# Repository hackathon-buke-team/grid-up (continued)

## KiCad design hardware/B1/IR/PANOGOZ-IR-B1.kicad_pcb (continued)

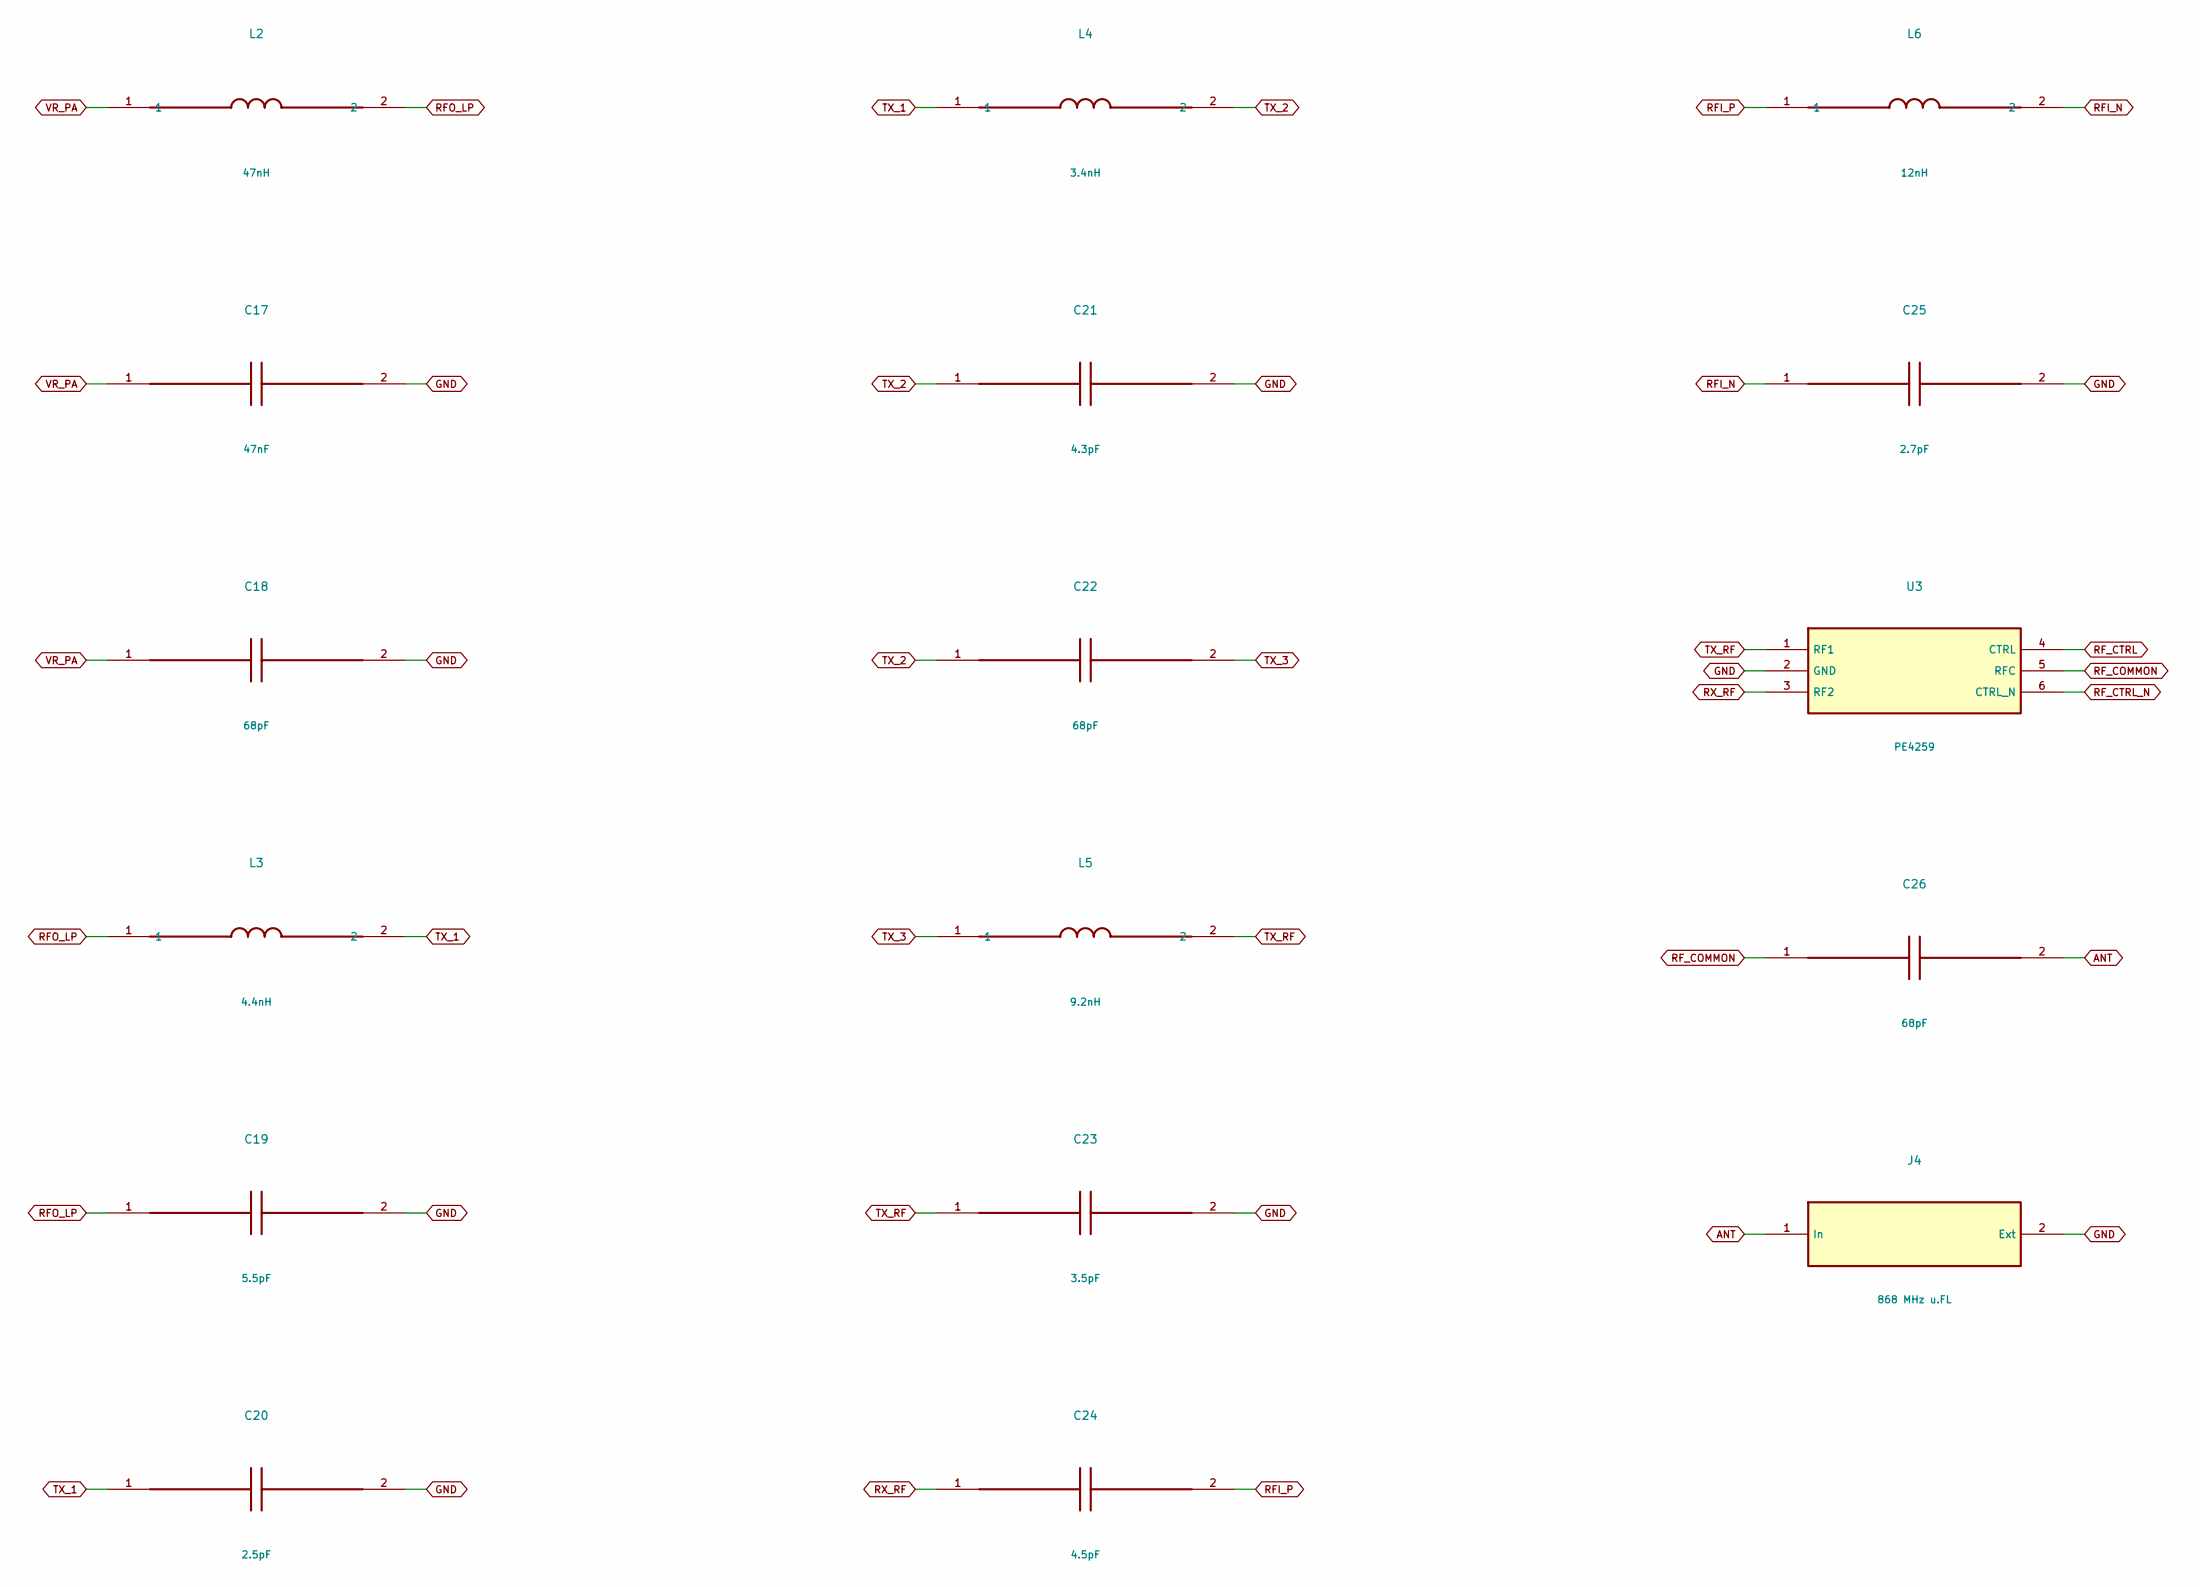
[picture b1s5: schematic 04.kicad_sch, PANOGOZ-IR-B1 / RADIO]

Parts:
C17: 47nF; C_0402_1005Metric; MPN X7R 16V 47nF
C18, C22, C26: 68pF; C_0402_1005Metric; MPN X7R 16V 68pF
C19: 5.5pF; C_0402_1005Metric; MPN X7R 16V 5.5pF
C20: 2.5pF; C_0402_1005Metric; MPN X7R 16V 2.5pF
C21: 4.3pF; C_0402_1005Metric; MPN X7R 16V 4.3pF
C23: 3.5pF; C_0402_1005Metric; MPN X7R 16V 3.5pF
C24: 4.5pF; C_0402_1005Metric; MPN X7R 16V 4.5pF
C25: 2.7pF; C_0402_1005Metric; MPN X7R 16V 2.7pF
J4: 868 MHz u.FL; U.FL_Hirose_U.FL-R-SMT-1_Vertical; MPN 868 MHz u.FL
L2: 47nH; L_0402_1005Metric; MPN 47nH
L3: 4.4nH; L_0402_1005Metric; MPN 4.4nH
L4: 3.4nH; L_0402_1005Metric; MPN 3.4nH
L5: 9.2nH; L_0402_1005Metric; MPN 9.2nH
L6: 12nH; L_0402_1005Metric; MPN 12nH
U3: PE4259; SOT-363_SC-70-6; MPN PE4259

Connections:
ANT: C26.2, J4.1 (In)
GND: C17.2, C18.2, C19.2, C20.2, C21.2, C23.2, C25.2, J4.2 (Ext), U3.2 (GND); also elsewhere on the board
RFI_N: C25.1, L6.2; also elsewhere on the board
RFI_P: C24.2, L6.1; also elsewhere on the board
RFO_LP: C19.1, L2.2, L3.1; also elsewhere on the board
RF_COMMON: C26.1, U3.5 (RFC)
RF_CTRL: U3.4 (CTRL); also elsewhere on the board
RF_CTRL_N: U3.6 (CTRL_N); also elsewhere on the board
RX_RF: C24.1, U3.3 (RF2)
TX_1: C20.1, L3.2, L4.1
TX_2: C21.1, C22.1, L4.2
TX_3: C22.2, L5.1
TX_RF: C23.1, L5.2, U3.1 (RF1)
VR_PA: C17.1, C18.1, L2.1; also elsewhere on the board

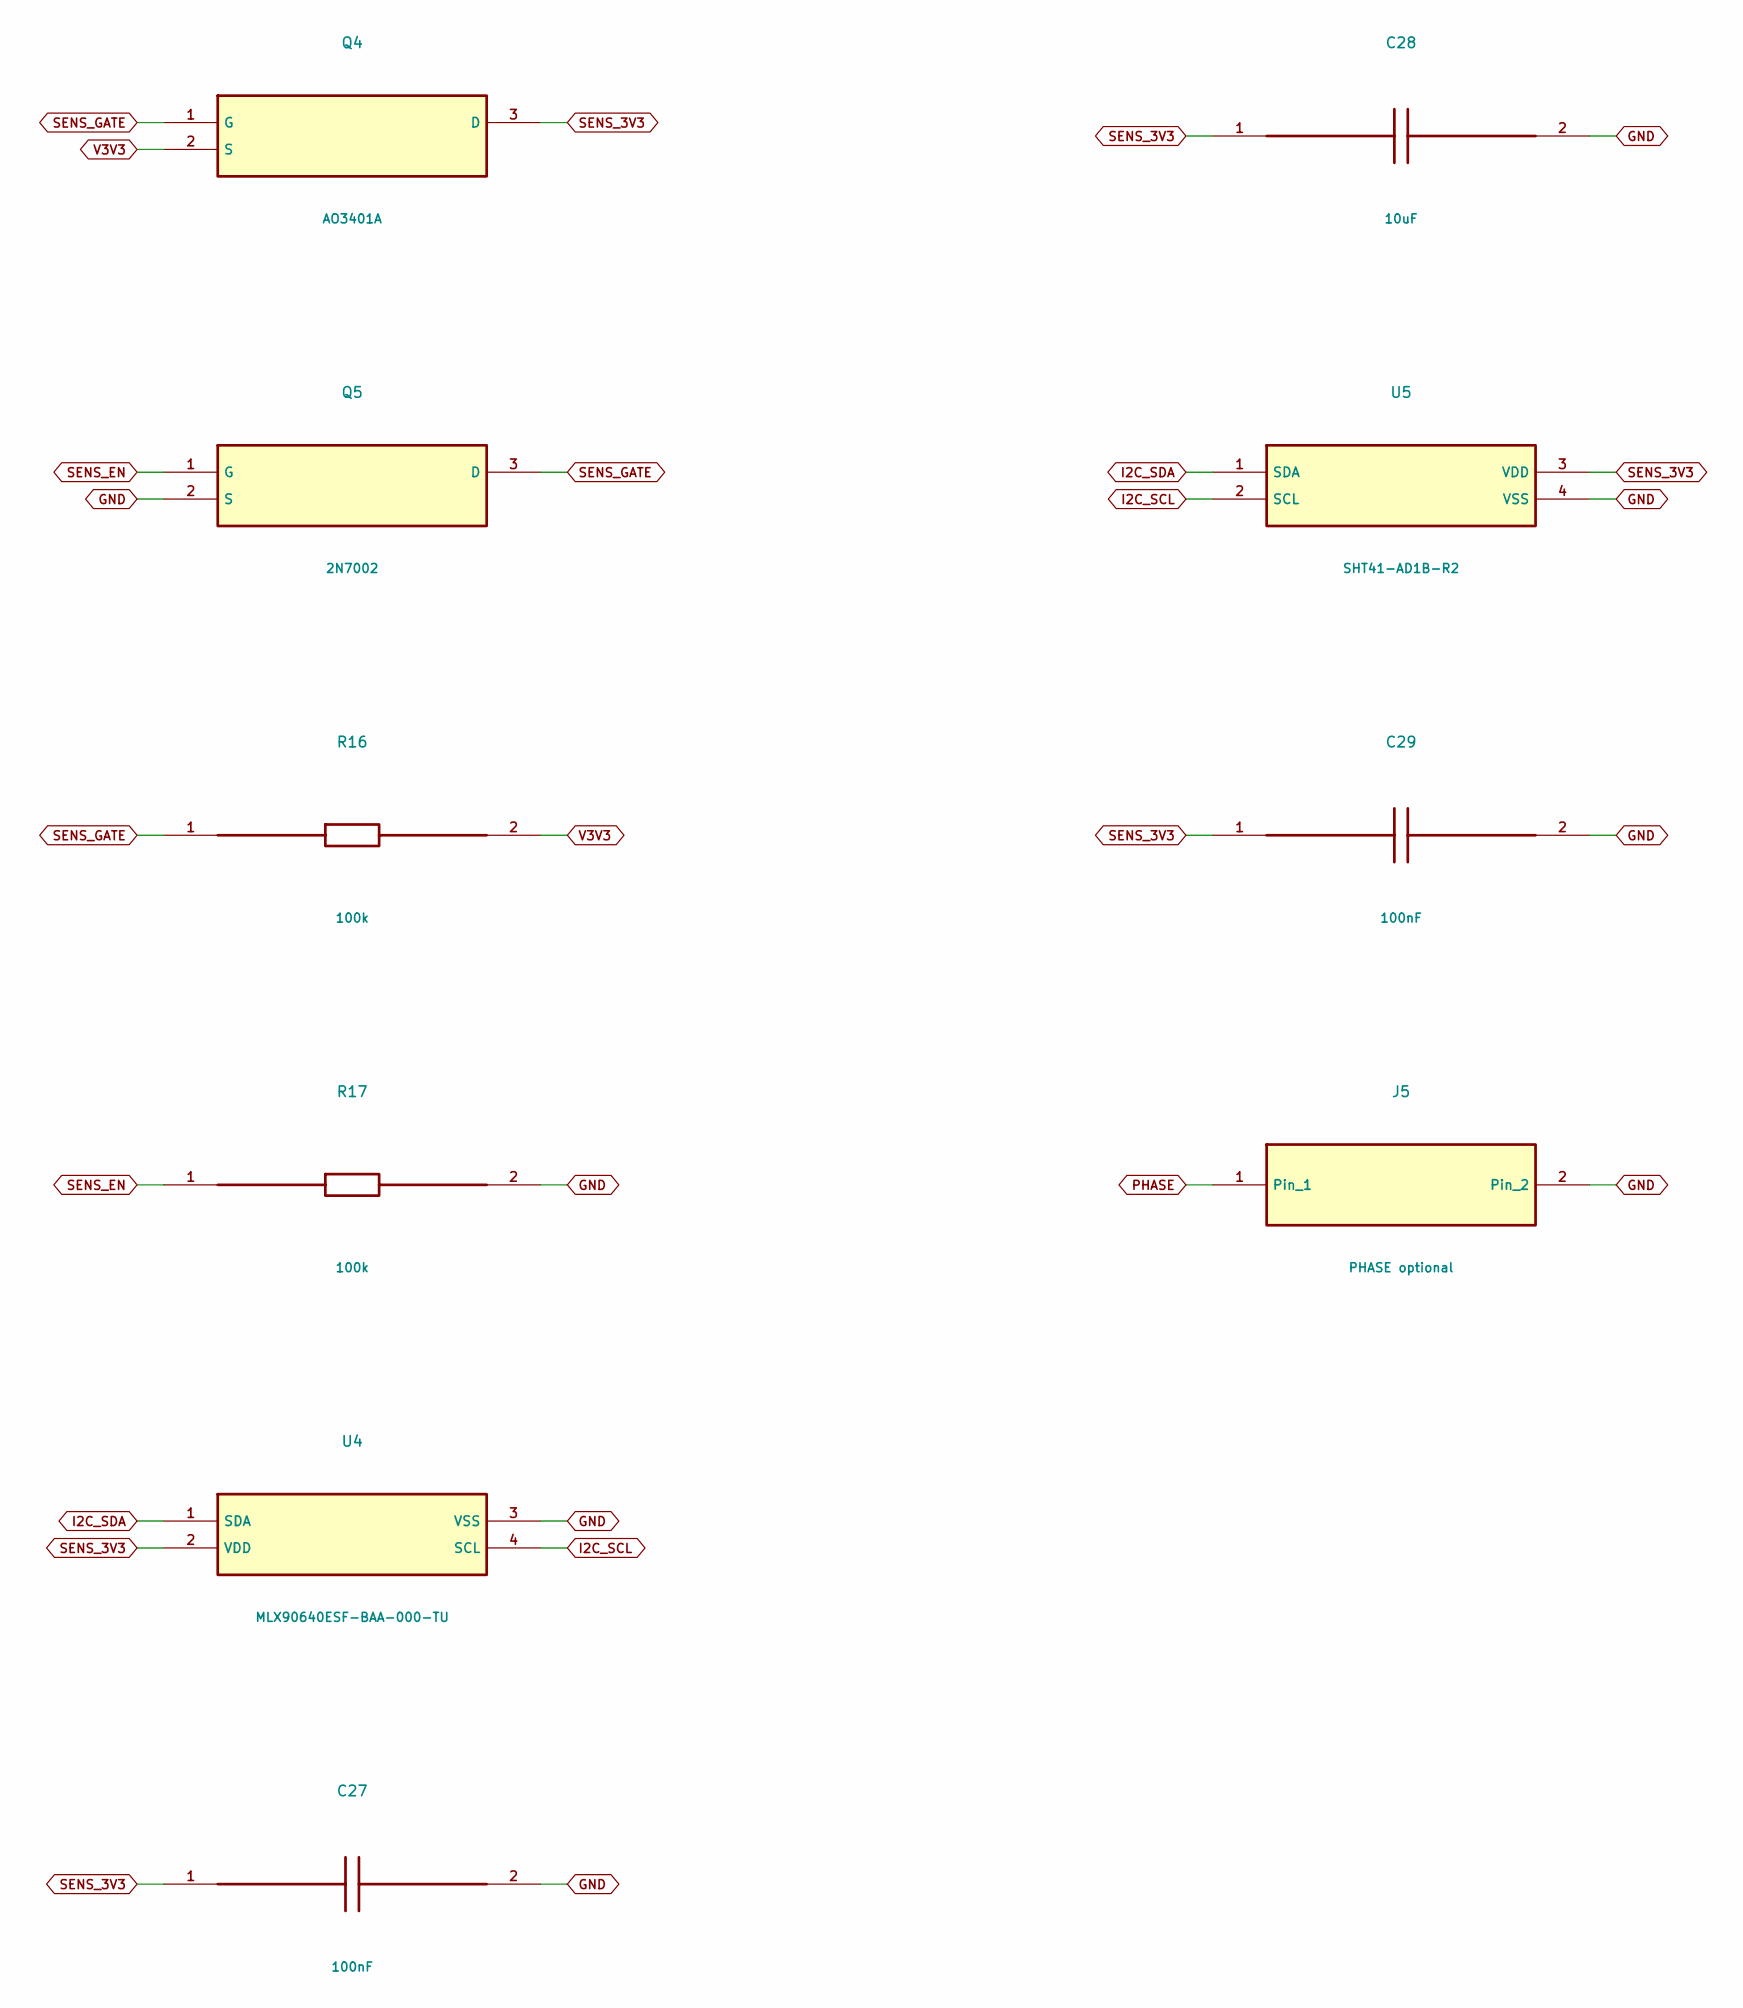
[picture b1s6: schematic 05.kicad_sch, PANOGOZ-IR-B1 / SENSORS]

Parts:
C27, C29: 100nF; C_0402_1005Metric; MPN X7R 16V 100nF
C28: 10uF; C_0805_2012Metric; MPN X7R 16V 10uF
J5: PHASE optional; JST_SH_SM02B-SRSS-TB_1x02-1MP_P1.00mm_Horizontal; MPN PHASE optional
Q4: AO3401A; SOT-23; MPN AO3401A
Q5: 2N7002; SOT-23; MPN 2N7002
R16, R17: 100k; R_0402_1005Metric; MPN 1% thick film 100k
U4: MLX90640ESF-BAA-000-TU; TO-39-4_Window; MPN MLX90640ESF-BAA-000-TU
U5: SHT41-AD1B-R2; Sensirion_DFN-4_1.5x1.5mm_P0.8mm_SHT4x_NoCentralPad; MPN SHT41-AD1B-R2

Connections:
GND: C27.2, C28.2, C29.2, J5.2, Q5.2 (S), R17.2, U4.3 (VSS), U5.4 (VSS); also elsewhere on the board
I2C_SCL: U4.4 (SCL), U5.2 (SCL); also elsewhere on the board
I2C_SDA: U4.1 (SDA), U5.1 (SDA); also elsewhere on the board
PHASE: J5.1; also elsewhere on the board
SENS_3V3: C27.1, C28.1, C29.1, Q4.3 (D), U4.2 (VDD), U5.3 (VDD); also elsewhere on the board
SENS_EN: Q5.1 (G), R17.1; also elsewhere on the board
SENS_GATE: Q4.1 (G), Q5.3 (D), R16.1
V3V3: Q4.2 (S), R16.2; also elsewhere on the board

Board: 4 copper layers, 70 parts (1 on the bottom side), 47 nets, no tracks yet.

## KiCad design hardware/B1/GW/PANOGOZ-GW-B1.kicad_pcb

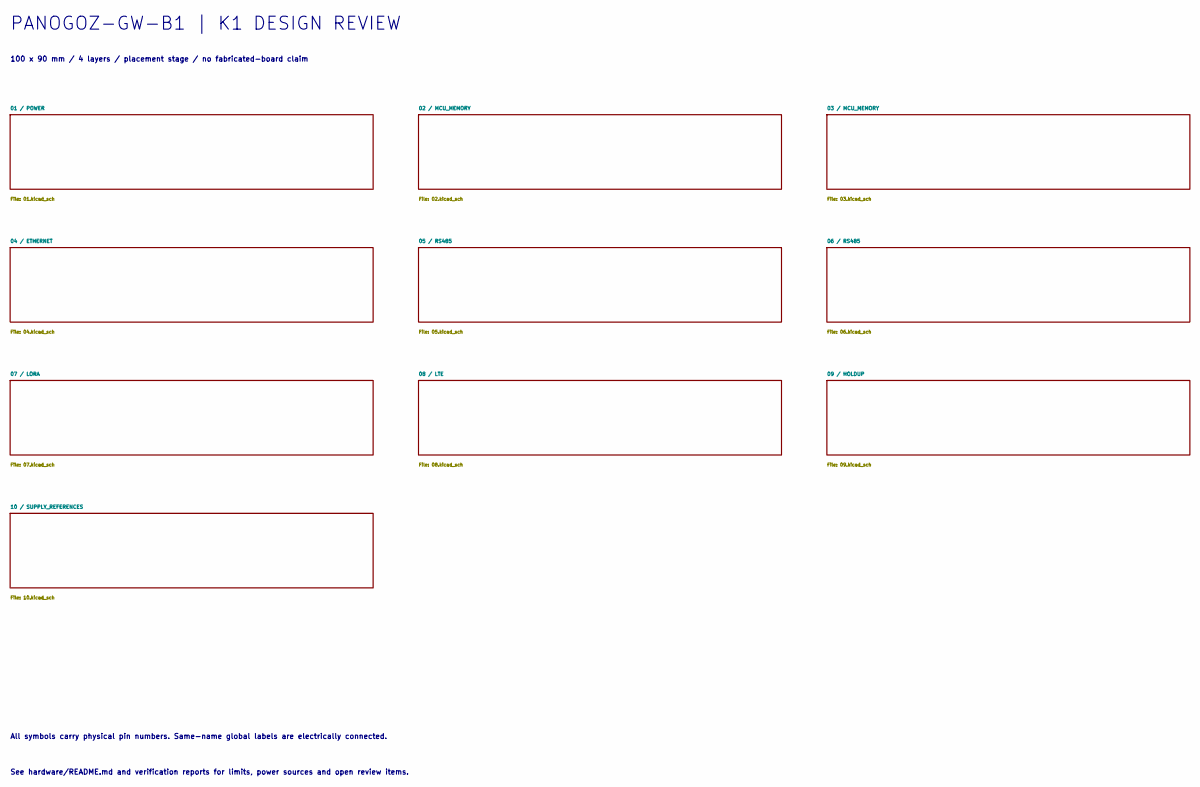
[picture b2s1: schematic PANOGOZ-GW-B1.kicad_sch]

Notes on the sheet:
PANOGOZ-GW-B1 | K1 DESIGN REVIEW
100 x 90 mm / 4 layers / placement stage / no fabricated-board claim
All symbols carry physical pin numbers. Same-name global labels are electrically connected.
See hardware/README.md and verification reports for limits, power sources and open review items.

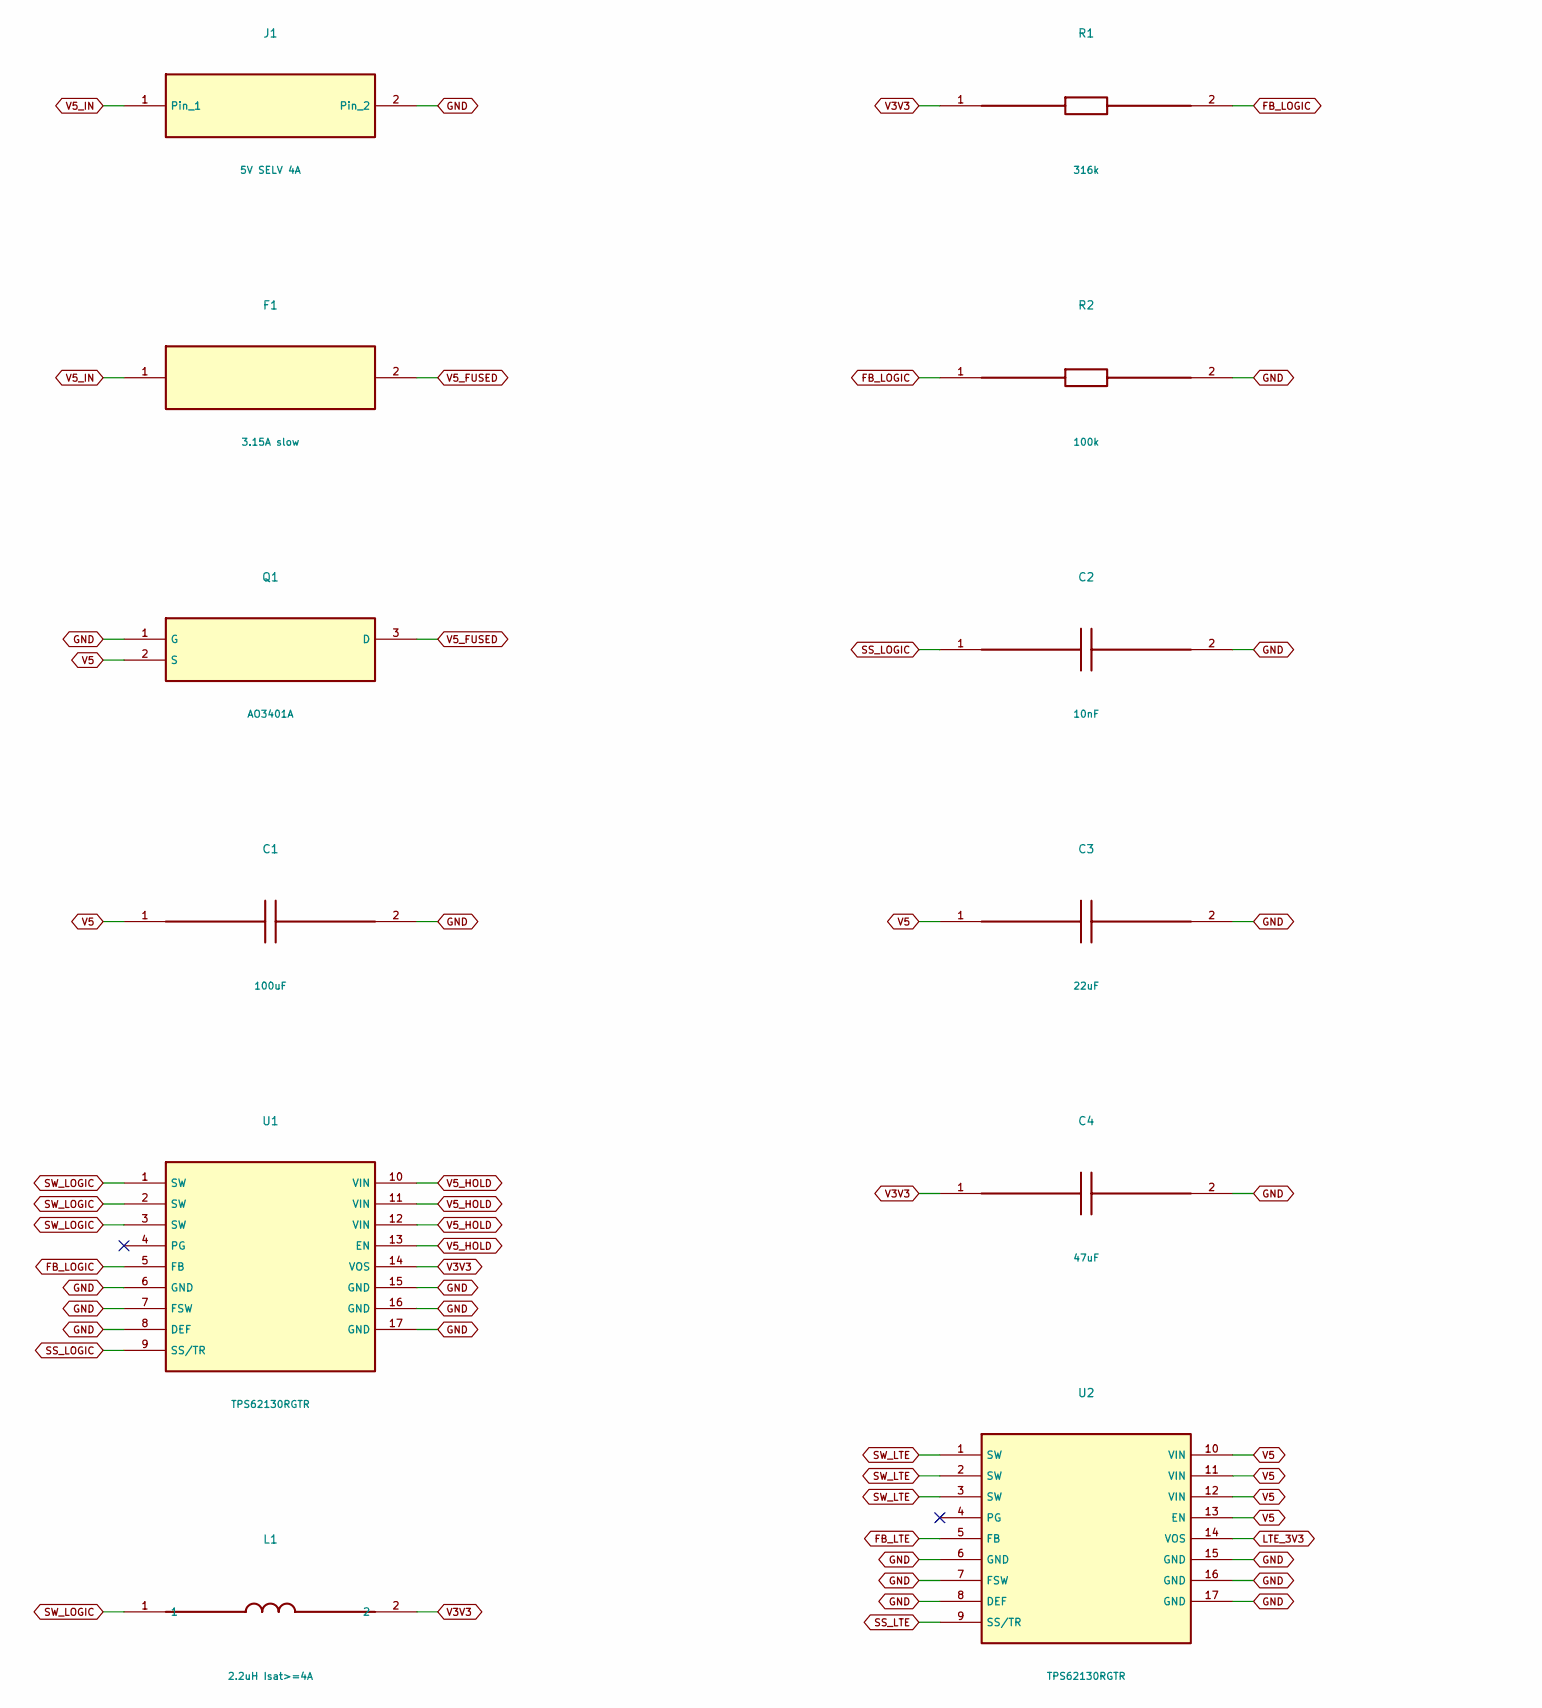
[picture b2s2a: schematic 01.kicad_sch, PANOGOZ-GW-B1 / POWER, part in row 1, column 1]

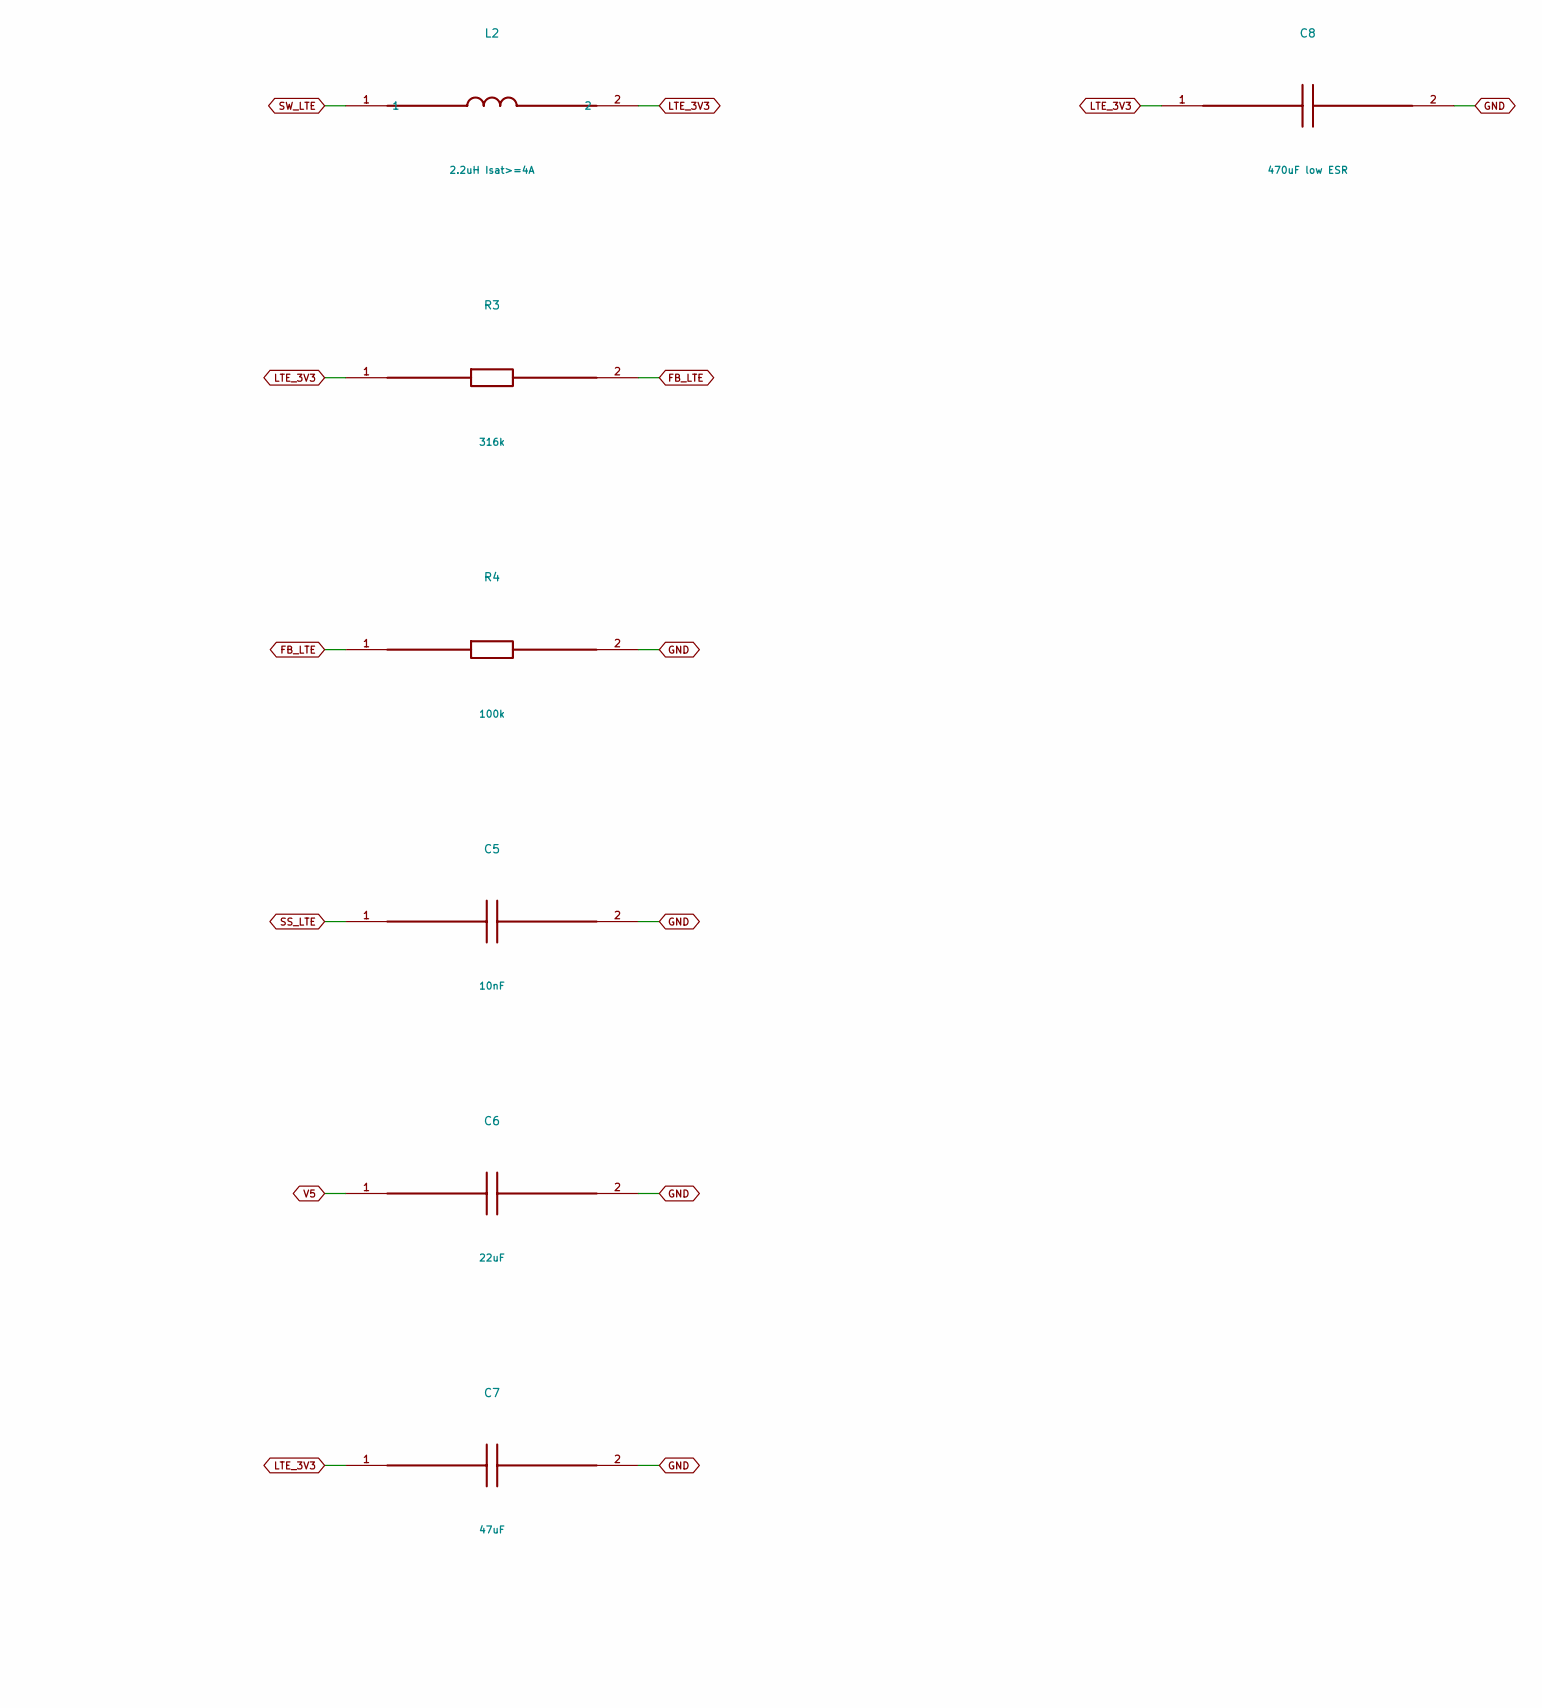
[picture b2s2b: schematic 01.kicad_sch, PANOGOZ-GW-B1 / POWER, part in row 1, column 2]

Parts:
C1: 100uF; C_1210_3225Metric; MPN X7R 16V 100uF
C2, C5: 10nF; C_0402_1005Metric; MPN X7R 16V 10nF
C3, C6: 22uF; C_0805_2012Metric; MPN X7R 16V 22uF
C4, C7: 47uF; C_1210_3225Metric; MPN X7R 16V 47uF
C8: 470uF low ESR; CP_Elec_8x10; MPN X7R 16V 470uF low ESR
F1: 3.15A slow; Fuse_1206_3216Metric; MPN 3.15A slow
J1: 5V SELV 4A; TerminalBlock_Phoenix_MKDS-1,5-2-5.08_1x02_P5.08mm_Horizont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; MPN 5V SELV 4A
L1, L2: 2.2uH Isat>=4A; L_1210_3225Metric; MPN 2.2uH Isat>=4A
Q1: AO3401A; SOT-23; MPN AO3401A
R1, R3: 316k; R_0402_1005Metric; MPN 1% thick film 316k
R2, R4: 100k; R_0402_1005Metric; MPN 1% thick film 100k
U1, U2: TPS62130RGTR; VQFN-16-1EP_3x3mm_P0.5mm_EP1.68x1.68mm_ThermalVias; MPN TPS62130RGTR

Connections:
FB_LOGIC: R1.2, R2.1, U1.5 (FB)
FB_LTE: R3.2, R4.1, U2.5 (FB)
GND: C1.2, C2.2, C3.2, C4.2, C5.2, C6.2, C7.2, C8.2, J1.2, Q1.1 (G), R2.2, R4.2, U1.6 (GND), U1.7 (FSW), U1.8 (DEF), U1.15 (GND), U1.16 (GND), U1.17 (GND), U2.6 (GND), U2.7 (FSW), U2.8 (DEF), U2.15 (GND), U2.16 (GND), U2.17 (GND); also elsewhere on the board
LTE_3V3: C7.1, C8.1, L2.2, R3.1, U2.14 (VOS); also elsewhere on the board
SS_LOGIC: C2.1, U1.9 (SS/TR)
SS_LTE: C5.1, U2.9 (SS/TR)
SW_LOGIC: L1.1, U1.1 (SW), U1.2 (SW), U1.3 (SW)
SW_LTE: L2.1, U2.1 (SW), U2.2 (SW), U2.3 (SW)
V3V3: C4.1, L1.2, R1.1, U1.14 (VOS); also elsewhere on the board
V5: C1.1, C3.1, C6.1, Q1.2 (S), U2.10 (VIN), U2.11 (VIN), U2.12 (VIN), U2.13 (EN); also elsewhere on the board
V5_FUSED: F1.2, Q1.3 (D)
V5_HOLD: U1.10 (VIN), U1.11 (VIN), U1.12 (VIN), U1.13 (EN); also elsewhere on the board
V5_IN: F1.1, J1.1
